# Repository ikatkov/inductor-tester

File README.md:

# (Power) Inductor saturation current tester

~60A max current. Power supply 5-25V.
Based on http://elm-chan.org/works/lchk/report.html

You will need an oscilloscope to take measurements.

# Theory

Once powered, the capacitor bank charges up. The circuit fires off a variable-width pulse into the MOSFET gate. MOSFET turns ON and short-circuits the inductor to the capacitor power bank. The current starts to rise linearly until the saturation point is reached. Once the inductor is saturated, it behaves like an ohmic piece of wire, and the current increases exponentially until the pulse is over, and the MOSFET is switched OFF. Saturation is a knee, not a sharp point. So you have some wiggle room in what current you designate as a "saturation current." Before the saturation point and including the "knee region," inductance will be higher than labeled. Once saturated sufficiently - inductance will drop.

This is how a regular plot should look like

This is how oversaturation, should look like

Commercial manufacturers pick the point where a power inductor loses 20-30% of its labeled inductance. One can safely operate inductors at x1.3-1.5 their knee point.

You take voltage drop measurements across 0.1 Ohm resistor, multiply by 10 and get current in Amps flowing through your inductor under test. `I = V*10`

You can also compute actual inductance be taking your supply voltage and dividing by the voltage slope. 
`L = Vs * Δt / ΔI`. 

# Practical operations

See "sort-of" instructions video https://www.youtube.com/watch?v=3Y_WcuIenSM
Notice that although their PCB is labeled 1us..50us. It's impossible to get a positive pulse width of less than 10uS with NE555. One can replace it with other astable timers ICs, but you need a separate MOSFET driving circuitry. NE555 raising and falling times ~350ns, with a max current of 200mA, which is not enough to quickly switch power MOSFETs ON/OFF. The MOSFET will be in its linear region for some time. Therefore the trigger pulse is set to ~50Hz, letting MOSFET cool down between pulses. Also, notice that the current sense shunt, capacitor bank ESR and traces resistance limits max current to ~56A.
You would want to rig some sort of replacable solder-pads on the top of the PCB, so you can finger-press small SMD inductors to it and solder large ones to take measurements. There are header holes for this.

* Unplug the power
* Turn the potentiometer all the way counterclockwise. Set the duration selector jumper to the shortest range. 
* Connect oscilloscope probes
* Plug the power
* Look at the oscilloscope
* Turn the potentiometer clockwise (increasing the pulse width) until you see the saturation knee
* If you still see a linear ramp, unplug, change the duration selector jumper to the next position, turn the potentiometer all the way counterclockwise and repeat
* Take measurements

# Manufacturing

[PCB STEP model](main.step)

[Full STEP model](enclosure.step)

[Full Fusion360 model](enclosure.f3zki)

[PCB Thermal Heat Flow Analysis](heat.jpg)

# Future improvements

NE555 is a compromise for this project purpose, you need two of them to deliver a short pulse, but it can also source 200ma current by itself. An alternative design is to use a cheap MCU and a MOSFET driver. Same PCB footprint, but better timing (no need to mess around with jumpers) and higher currents to turn the MOSFET on and off. High gate current also means "ringing" 
on MOSFET turn on, which in turn manifests itself as current measurements ringing. For large inductors it is OK, for small (SMD) it might be hard to take measurements. With a better MCU one can even do automatic pulse control. This gets complex fast. 16 MHz Arduino is ~ 100uS per ADC sample. 

`For a 16 MHz Arduino the ADC clock is set to 16 MHz/128 = 125 KHz. Each conversion in AVR takes 13 ADC clocks so 125 KHz /13 = 9615 Hz.`

As soon as you consider a fast external ADC, you start worry about crystal clock-jitter, temperature drift and SPI speed.

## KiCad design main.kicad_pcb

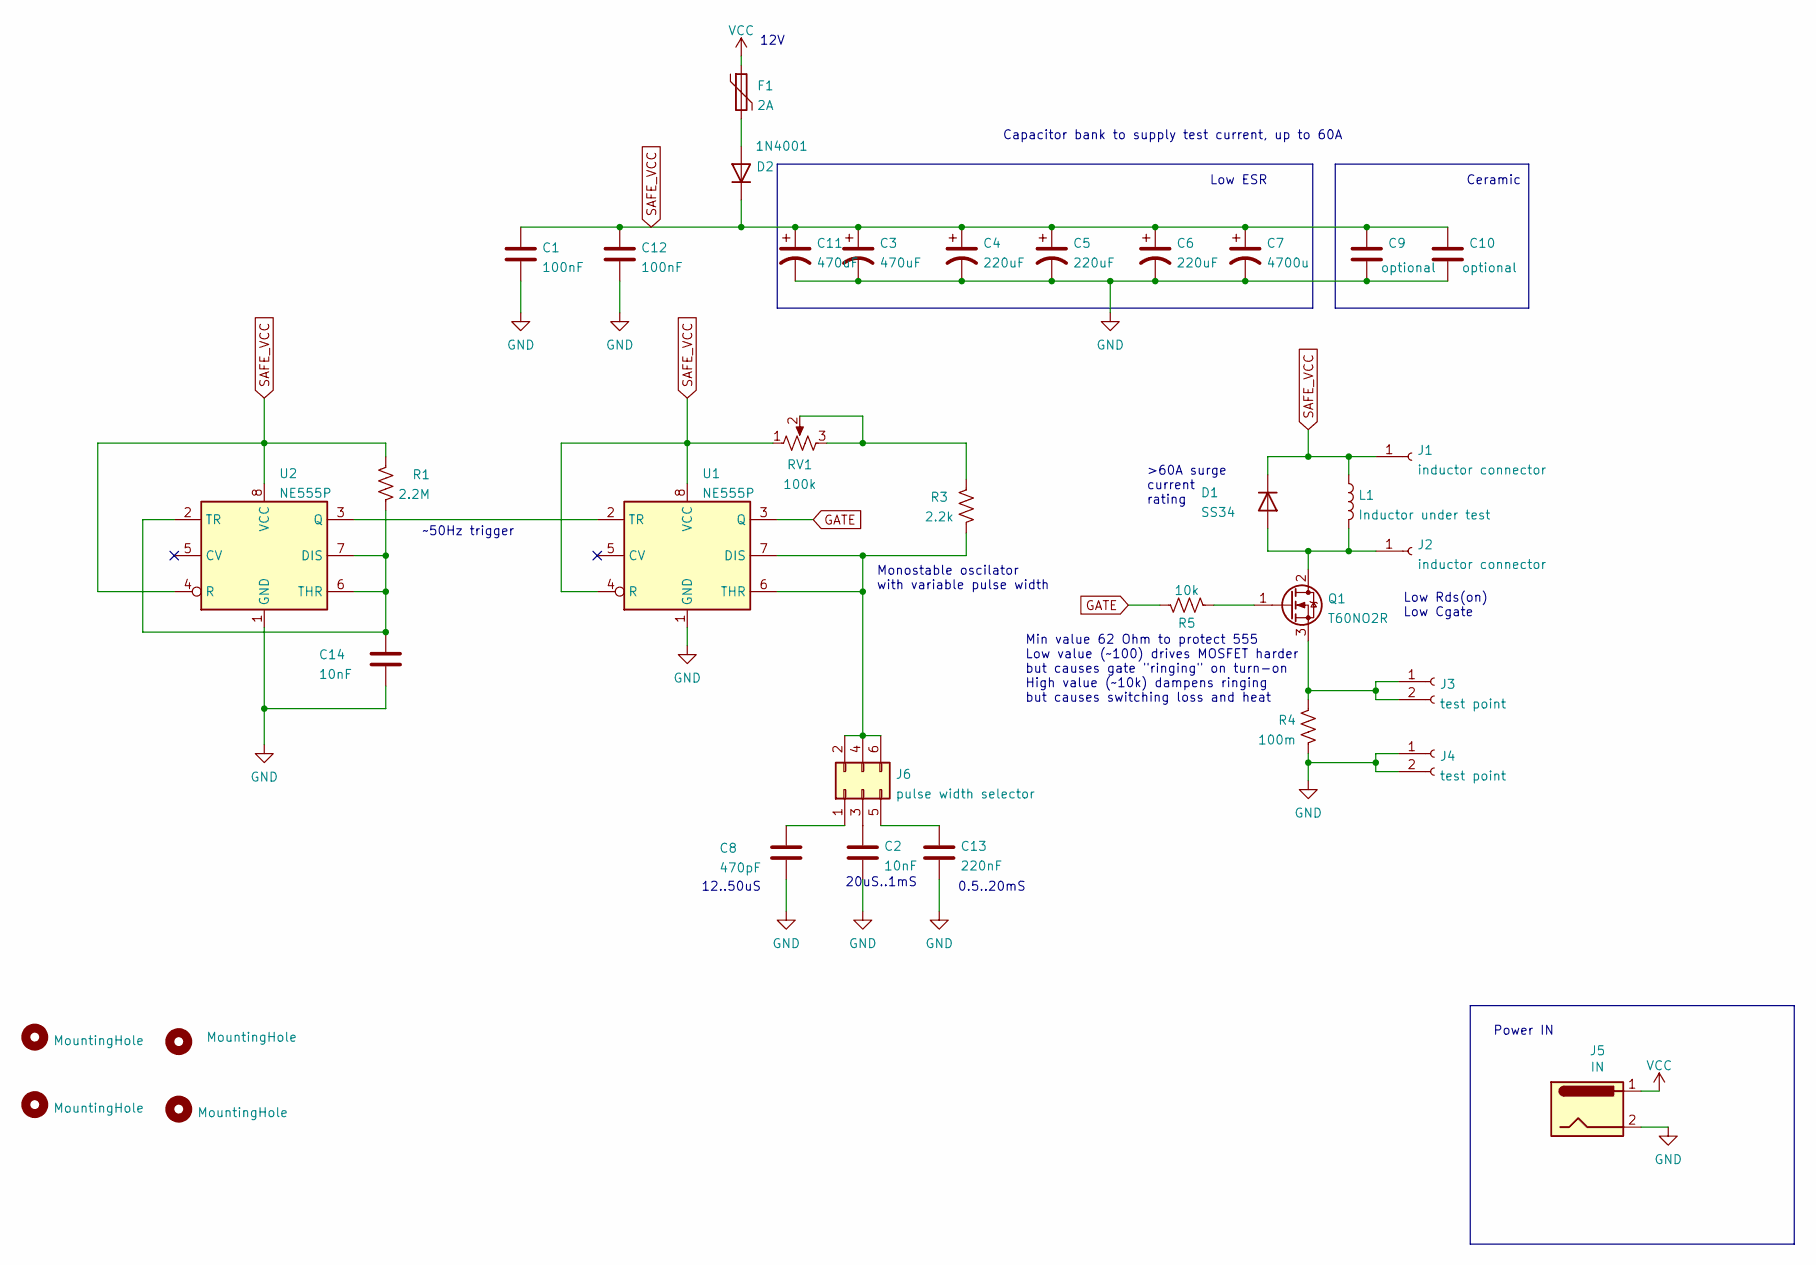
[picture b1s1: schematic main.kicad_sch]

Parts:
C1, C12: 100nF; C_1206_3216Metric
C2, C14: 10nF; C_1206_3216Metric
C3, C11: 470uF; CP_Radial_D10.0mm_P5.00mm
C4, C5, C6: 220uF; CP_Radial_D10.0mm_P5.00mm
C7: 4700u; CP_Radial_D18.0mm_P7.50mm
C8: 470pF; C_1206_3216Metric
C9, C10: optional; C_1206_3216Metric
C13: 220nF; C_1206_3216Metric
D1: SS34; D_SMA
D2: 1N4001; D_MELF
F1: 2A; R_MELF_MMB-0207
H1, H2, H3, H4: MountingHole; MountingHole_2.2mm_M2
J1, J2: inductor connector; SolderWirePad_1x01_SMD_2x4mm
J3, J4: test point; PinHeader_1x02_P2.54mm_Vertical
J5: IN; BarrelJack_Horizontal
J6: pulse width selector; PinHeader_2x03_P2.54mm_Vertical
L1: Inductor under test
Q1: T60NO2R; TO-252-2
R1: 2.2M; R_0805_2012Metric
R3: 2.2k; R_0805_2012Metric
R4: 100m; R_2512_6332Metric
R5: 10k; R_0805_2012Metric
RV1: 100k; Potentiometer_Bourns_3296W_Vertical
U1, U2: NE555P; DIP-8_W7.62mm

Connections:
GATE: Q1.1 (G), R5.2
GND: C1.2, C2.2, C3.2, C4.2, C5.2, C6.2, C7.2, C8.2, C9.2, C10.2, C11.2, C12.2, C13.2, C14.2, J4.1, J4.2, J5.2, R4.2, U1.1 (GND), U2.1 (GND)
unnamed: C2.1, J6.3
unnamed: C8.1, J6.1
unnamed: C13.1, J6.5
unnamed: C14.1, R1.1, U2.2 (TR), U2.6 (THR), U2.7 (DIS)
unnamed: D1.2 (A), J2.1, L1.2, Q1.2 (D)
unnamed: D2.2 (A), F1.2
unnamed: J3.1, J3.2, Q1.3 (S), R4.1
unnamed: J6.2, J6.4, J6.6, R3.2, U1.6 (THR), U1.7 (DIS)
unnamed: R3.1, RV1.2, RV1.3
unnamed: R5.1, U1.3 (Q)
unnamed: U1.2 (TR), U2.3 (Q)
SAFE_VCC: C1.1, C3.1, C4.1, C5.1, C6.1, C7.1, C9.1, C10.1, C11.1, C12.1, D1.1 (K), D2.1 (K), J1.1, L1.1, R1.2, RV1.1, U1.4 (R), U1.8 (VCC), U2.4 (R), U2.8 (VCC)
VCC: F1.1, J5.1

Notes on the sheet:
Low ESR
Low Rds(on) Low Cgate
0.5..20mS
Power IN
12..50uS
20uS..1mS
12V
Capacitor bank to supply test current, up to 60A
>60A surge current rating
Ceramic
Monostable oscilator with variable pulse width
~50Hz trigger
Min value 62 Ohm to protect 555 Low value (~100) drives MOSFET harder but causes gate "ringing" on turn-on High value (~10k) dampens ringing but causes switching loss and heat

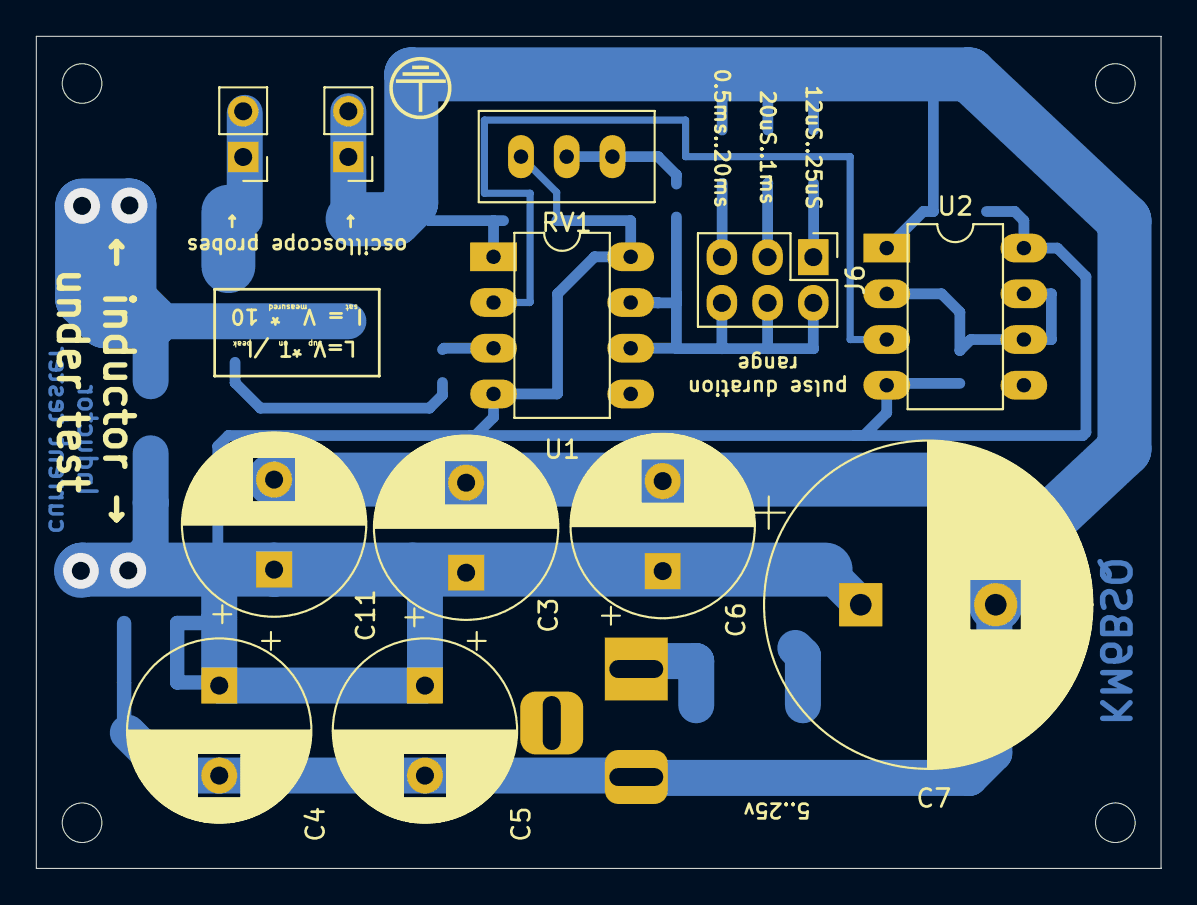
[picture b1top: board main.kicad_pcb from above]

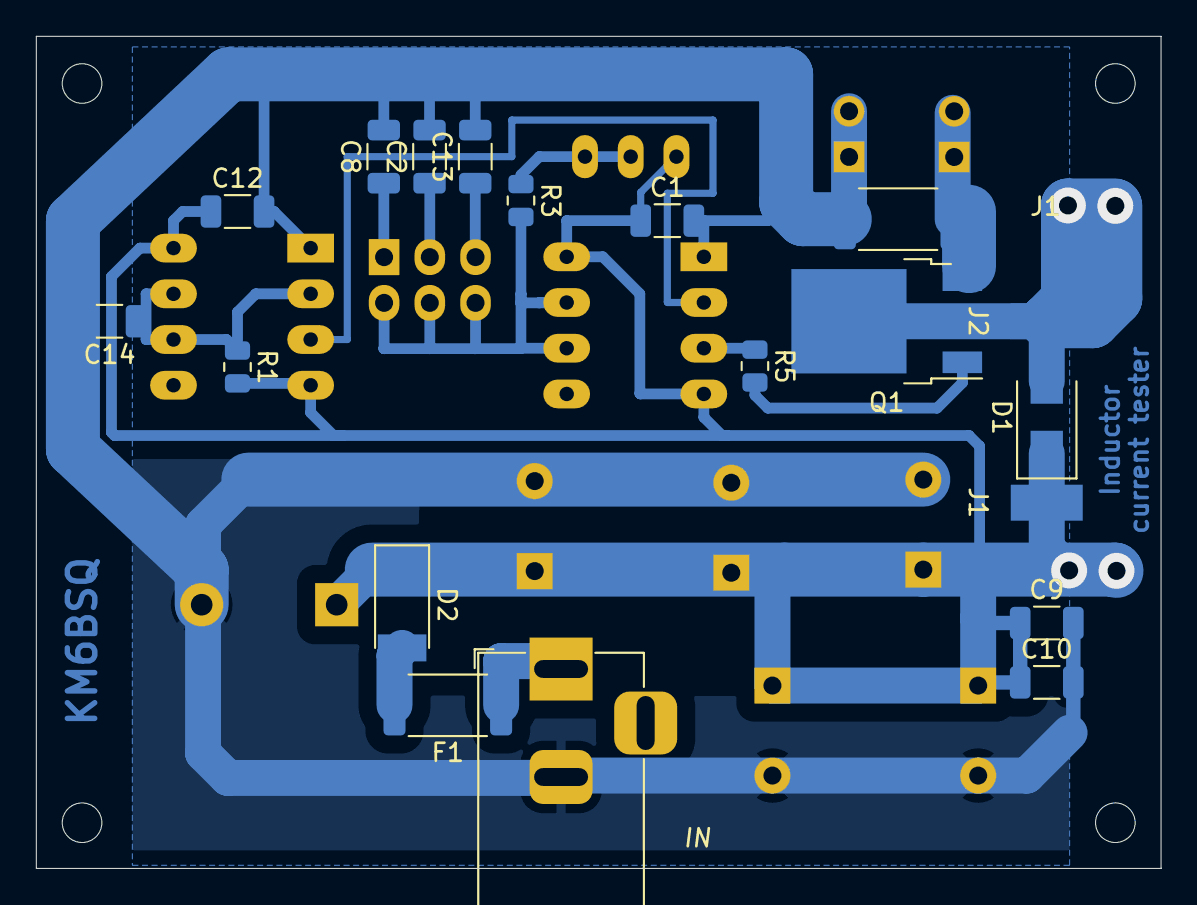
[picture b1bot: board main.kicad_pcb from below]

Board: 4 copper layers, 62.5 x 46.2 mm, 35 parts (19 on the bottom side), 15 nets.

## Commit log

2022-11-15 initial
2022-11-15 typo
2022-11-15 solder pad explanation
2022-11-15 formatting
2022-11-15 knee image
2022-11-21 more details
2022-11-21 update diode description
2022-11-22 readme update
2022-12-03 Changed gate resistor Add heat map
